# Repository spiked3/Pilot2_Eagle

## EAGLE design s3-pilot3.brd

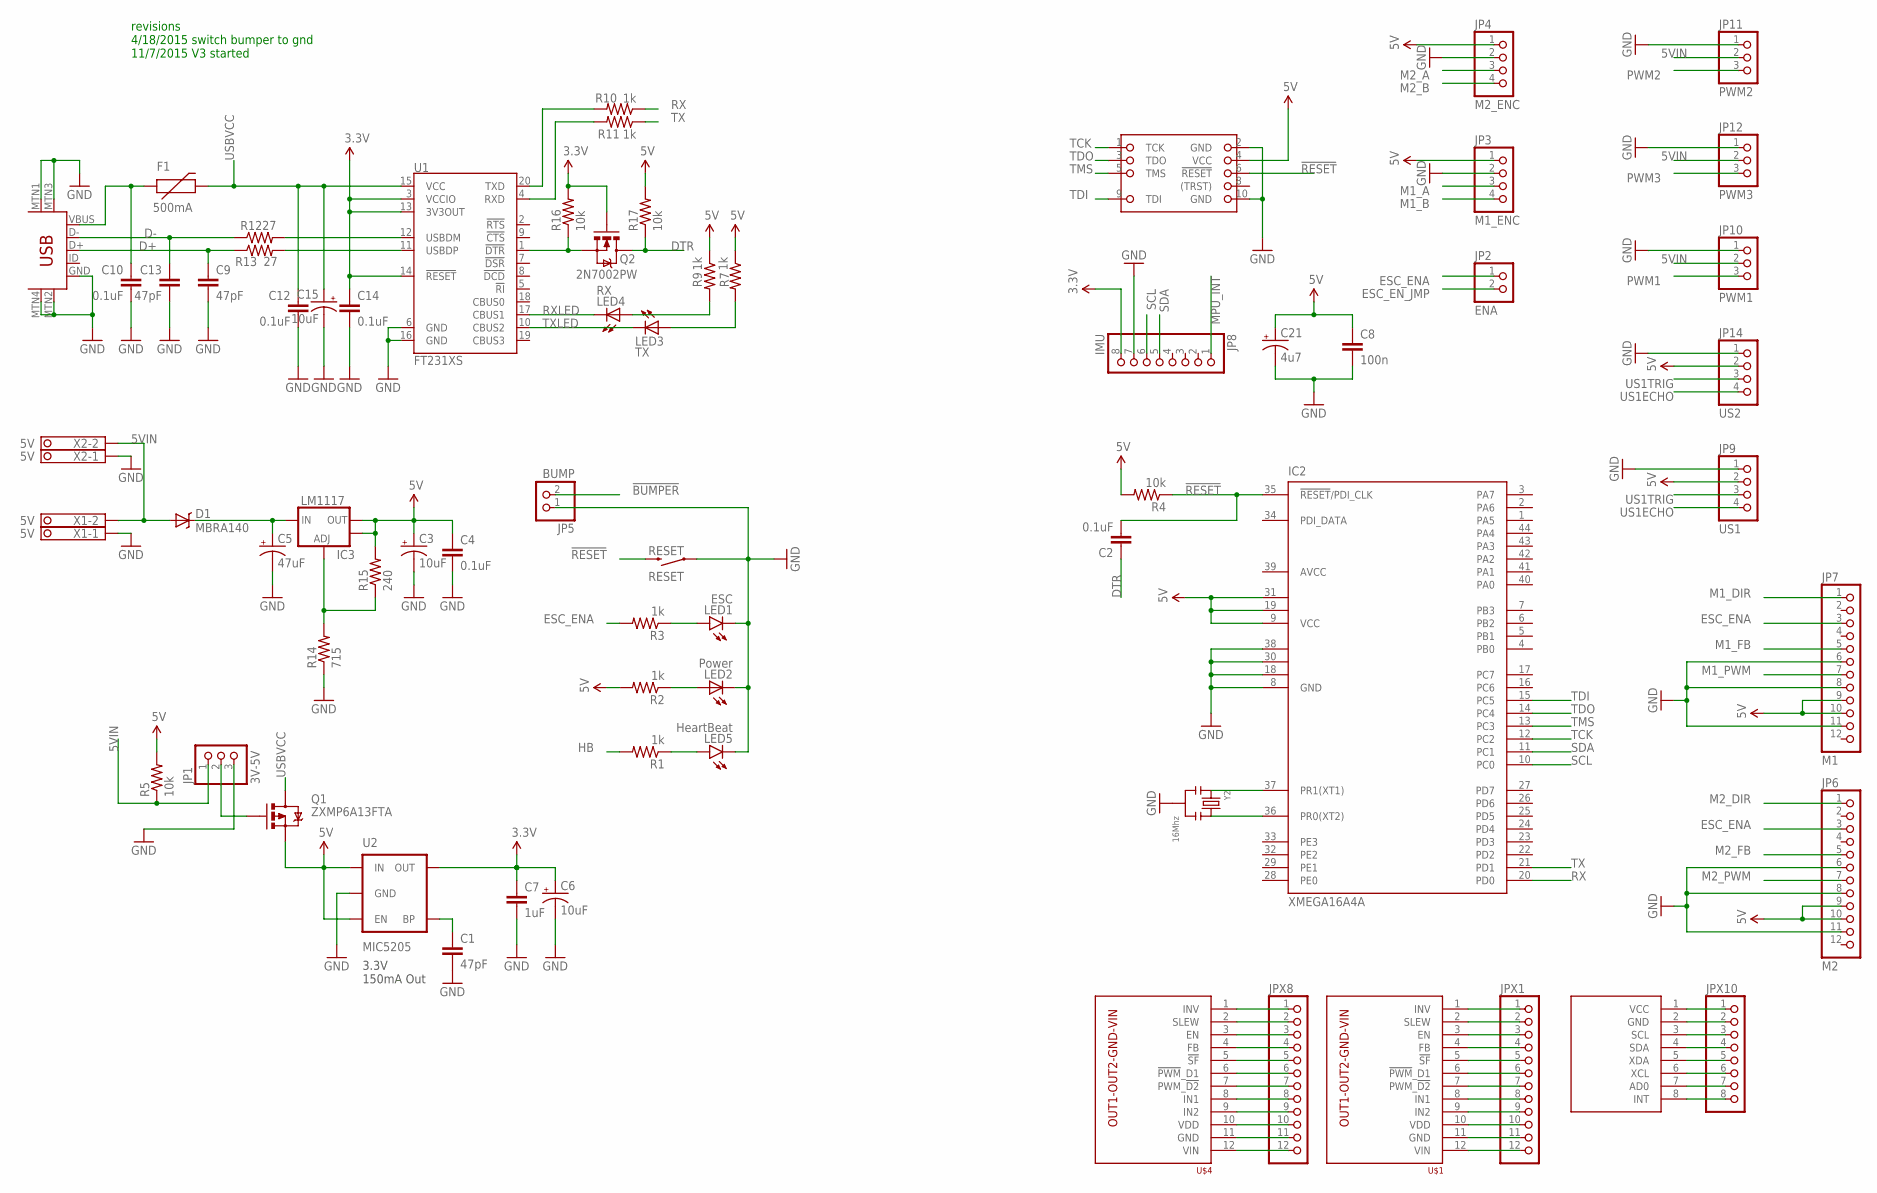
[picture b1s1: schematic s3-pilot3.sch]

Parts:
C1, C9, C13: 47pF; 0603-CAP
C2: 0.1uF; 0805
C3, C6, C15: 10uF; EIA3216
C4, C10, C12, C14: 0.1uF; 0603-CAP
C5: 47uF; PANASONIC_D
C7: 1uF; 0603-CAP
C8: 100n; 0603-CAP
C21: 4u7; EIA3216
D1: MBRA140; SMA-DIODE
F1: 500mA; PTC-1206
IC2: XMEGA16A4A; TQFP44
IC3: LM1117; SOT223
JP1: 3V-5V; 1X03
JP2: ENA; 1X02
JP3: M1_ENC; 1X04/90
JP4: M2_ENC; 1X04/90
JP5: BUMP; 1X02/90
JP6: M2; 1X12
JP7: M1; 1X12
JP8: IMU; 1X08
JP9: US1; 1X04/90
JP10: PWM1; 1X03/90
JP11: PWM2; 1X03/90
JP12: PWM3; 1X03/90
JP14: US2; 1X04/90
JPX1, JPX8: PINHD-1X12; 1X12
JPX10: PINHD-1X8; 1X08
LED1: ESC; LED-1206
LED2: Power; LED-1206
LED3: TX; LED-1206
LED4: RX; LED-1206
LED5: HeartBeat; LED-1206
MPU6050: MPU-6050-BO
Q1: ZXMP6A13FTA; SOT23-3
Q2: 2N7002PW; SOT323
R1, R2, R3, R7, R9, R10, R11: 1k; 0603-RES
R4, R5, R16, R17: 10k; 0603-RES
R12, R13: 27; 0603-RES
R14: 715; 0603-RES
R15: 240; 0603-RES
RESET: RESET; TACTILE_SWITCH_TALL
U1: FT231XS; SSOP20_L
U2: MIC5205; SOT23-5
U$1, U$4: M2; MC33926-SINGLE-BO
U$2: JTAG; 2X5/05
U$13: USB-MINIB-5PIN; USB-MINIB
X1, X2: 5V; 1751248
Y2: 16Mhz; SMD-KYOCERA-PBRV-H

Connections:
3.3V: C6.A (+), C7.1, C14.1, JP8.8, Q2.1 (G), R16.2, U1.3 (VCCIO), U1.13 (3V3OUT), U1.14 (!RESET), U2.5 (OUT)
5V: C3.A (+), C4.1, C8.1, C21.A (+), IC2.9 (VCC), IC2.19 (VCC1), IC2.31 (VCC2), IC3.2 (OUT), IC3.4 (OUT), JP3.1, JP4.1, JP6.9, JP6.10, JP7.9, JP7.10, JP9.2, JP14.2, Q1.2 (S), R2.2, R4.2, R5.2, R7.1, R9.1, R15.2, R17.2, U2.1 (IN), U2.3 (EN), U$2.4 (VCC)
5VIN: D1.A, JP1.1, JP10.2, JP11.2, JP12.2, R5.1, X1.2, X2.2
!BUMPER: JP5.2
!RESET: C2.2, IC2.35 (!RESET!/PDI_CLK), R4.1, RESET.B2 (2), U$2.6 (!RESET)
AVCC: IC2.39 (AVCC)
D+: C9.1, R13.1, U$13.D+
D-: C13.1, R12.1, U$13.D-
DTR: C2.1, Q2.3 (D), R17.1
ESC_ENA: JP2.1, JP6.3, JP7.3, R3.2
ESC_EN_JMP: JP2.2
GND: C1.2, C3.C (-), C4.2, C5.-, C6.C (-), C7.2, C8.2, C9.2, C10.2, C12.2, C13.2, C14.2, C15.C (-), C21.C (-), IC2.8 (GND), IC2.18 (GND1), IC2.30 (GND2), IC2.38 (GND3), JP1.3, JP3.2, JP4.2, JP5.1, JP6.6, JP6.8, JP6.11, JP7.6, JP7.8, JP7.11, JP8.7, JP9.1, JP10.1, JP11.1, JP12.1, JP14.1, LED1.C, LED2.C, LED5.C, R14.1, RESET.A2 (1), U1.6 (GND), U1.16 (GND), U2.2 (GND), U$2.2 (GND), U$2.10 (GND), U$13.GND, U$13.MTN1 (MTN2), U$13.MTN2 (MTN3), U$13.MTN3 (MTN1), U$13.MTN4, X1.1, X2.1, Y2.2
HB: R1.2
M1_A: JP3.3
M1_B: JP3.4
M1_DIR: JP7.1
M1_FB: JP7.5
M1_PWM: JP7.7
M2_A: JP4.3
M2_B: JP4.4
M2_DIR: JP6.1
M2_FB: JP6.5
M2_PWM: JP6.7
MPU_INT: JP8.1
unnamed: JPX8.1, U$4.1 (INV)
unnamed: LED2.A, R2.1
unnamed: JPX8.2, U$4.2 (SLEW)
unnamed: JPX8.3, U$4.3 (EN)
unnamed: R12.2, U1.12 (USBDM)
unnamed: R13.2, U1.11 (USBDP)
unnamed: LED3.A, R7.2
unnamed: LED4.A, R9.2
unnamed: C1.1, U2.4 (BP)
unnamed: Q2.2 (S), R16.1, U1.1 (!DTR)
unnamed: JPX10.1, MPU6050.1 (VCC)
unnamed: JPX10.2, MPU6050.2 (GND)
unnamed: IC3.1 (ADJ), R14.2, R15.1
unnamed: JPX10.3, MPU6050.3 (SCL)
unnamed: JPX10.4, MPU6050.4 (SDA)
unnamed: JPX1.1, U$1.1 (INV)
unnamed: JPX10.5, MPU6050.5 (XDA)
unnamed: JPX10.6, MPU6050.6 (XCL)
unnamed: LED5.A, R1.1
unnamed: JPX10.7, MPU6050.7 (AD0)
unnamed: LED1.A, R3.1
unnamed: JP1.2, Q1.1 (G)
unnamed: JPX1.2, U$1.2 (SLEW)
unnamed: JPX10.8, MPU6050.8 (INT)
unnamed: JPX8.4, U$4.4 (FB)
unnamed: JPX8.5, U$4.5 (!SF)
unnamed: JPX8.6, U$4.6 (!PWM!_D1)
unnamed: JPX8.7, U$4.7 (PWM_!D2)
unnamed: JPX8.8, U$4.8 (IN1)
unnamed: JPX8.9, U$4.9 (IN2)
unnamed: JPX8.10, U$4.10 (VDD)
unnamed: JPX8.11, U$4.11 (GND)
unnamed: JPX8.12, U$4.12 (VIN)
unnamed: IC2.36 (PR0(XT2)), Y2.3
unnamed: JPX1.3, U$1.3 (EN)
unnamed: JPX1.4, U$1.4 (FB)
unnamed: JPX1.5, U$1.5 (!SF)
unnamed: IC2.37 (PR1(XT1)), Y2.1
unnamed: JPX1.6, U$1.6 (!PWM!_D1)
unnamed: JPX1.7, U$1.7 (PWM_!D2)
unnamed: JPX1.8, U$1.8 (IN1)
unnamed: JPX1.9, U$1.9 (IN2)
unnamed: JPX1.10, U$1.10 (VDD)
unnamed: JPX1.11, U$1.11 (GND)
unnamed: JPX1.12, U$1.12 (VIN)
PISUPPLY: C5.+, D1.C, IC3.3 (IN)
PWM1: JP10.3
PWM2: JP11.3
PWM3: JP12.3
RX: IC2.20 (PD0), R10.1
RXD: R11.2, U1.4 (RXD)
RXLED: LED4.C, U1.17 (CBUS1)
SCL: IC2.10 (PC0), JP8.6
SDA: IC2.11 (PC1), JP8.5
TCK: IC2.12 (PC2), U$2.1 (TCK)
TDI: IC2.15 (PC5), U$2.9 (TDI)
TDO: IC2.14 (PC4), U$2.3 (TDO)
TMS: IC2.13 (PC3), U$2.5 (TMS)
TX: IC2.21 (PD1), R11.1
TXD: R10.2, U1.20 (TXD)
TXLED: LED3.C, U1.10 (CBUS2)
US1ECHO: JP9.4, JP14.4
US1TRIG: JP9.3, JP14.3
USBVCC: C12.1, C15.A (+), F1.2, Q1.3 (D), U1.15 (VCC)
VUSB: C10.1, F1.1, U$13.VBUS

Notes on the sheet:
revisions 4/18/2015 switch bumper to gnd 11/7/2015 V3 started
3.3V 150mA Out

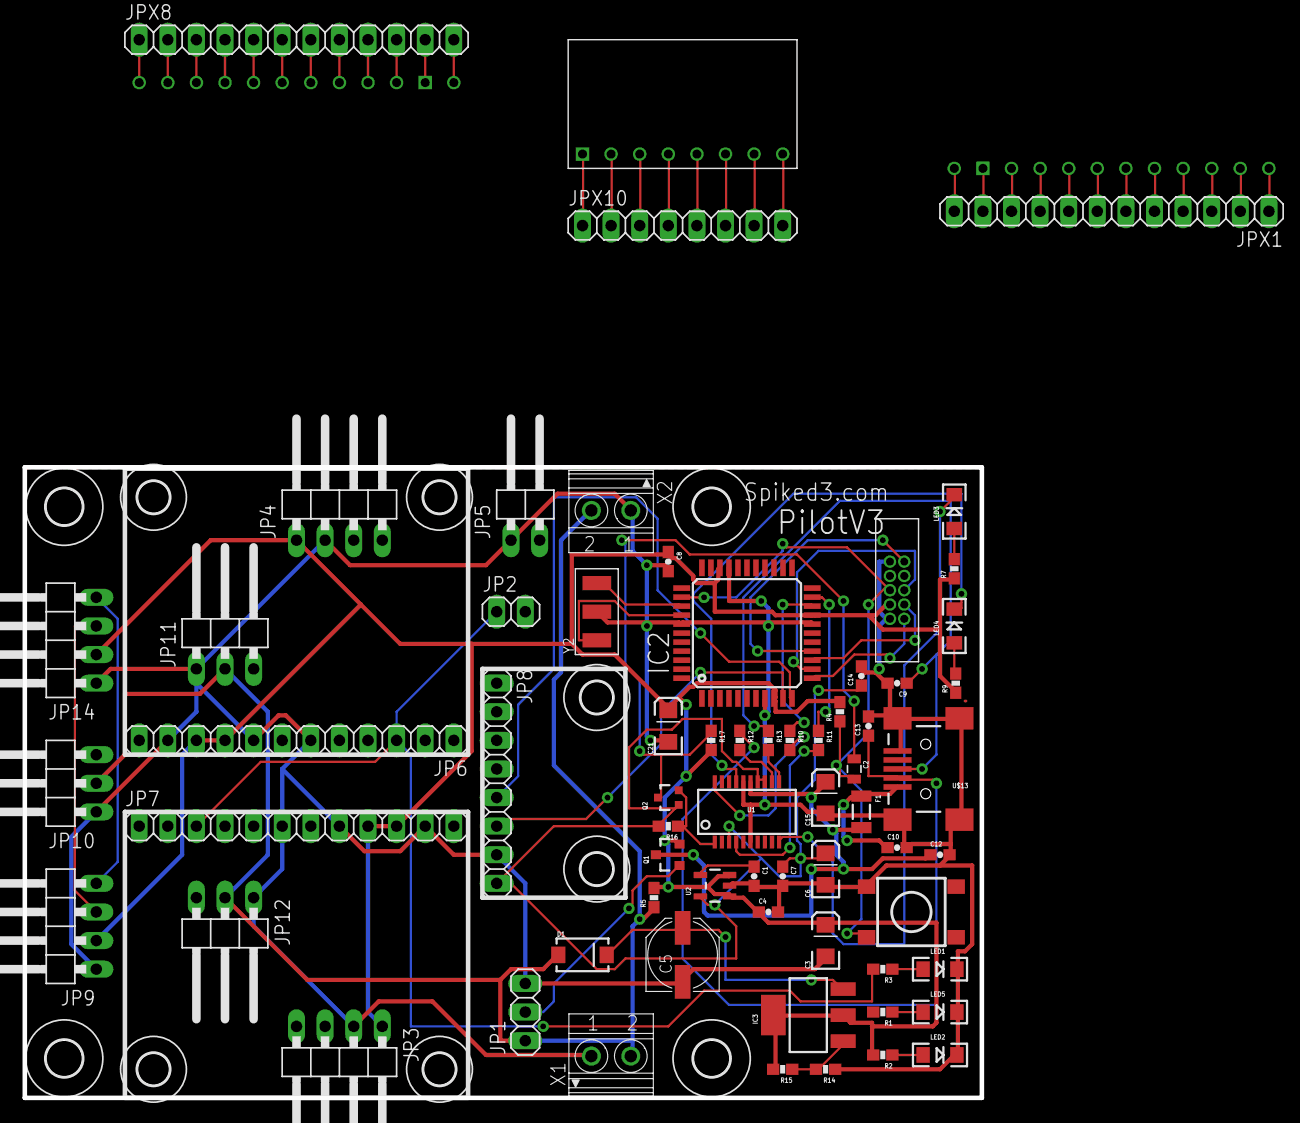
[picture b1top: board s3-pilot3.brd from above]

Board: 2 copper layers, 85.0 x 56.0 mm, 78 parts (0 on the bottom side), 71 nets.

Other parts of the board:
E$1, E$4, E$12, E$15, E$16, E$17: 2,8
E$2, E$3, E$5, E$6: 3,2

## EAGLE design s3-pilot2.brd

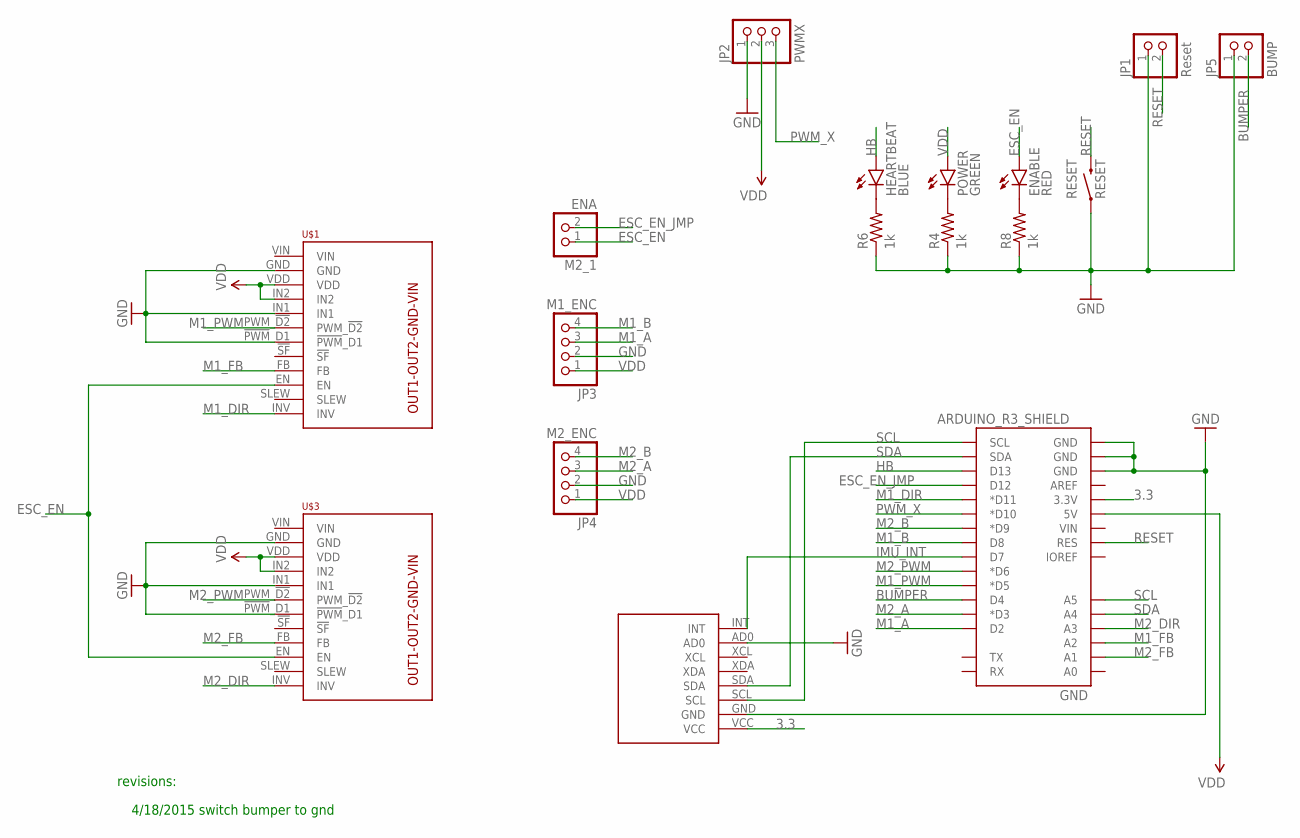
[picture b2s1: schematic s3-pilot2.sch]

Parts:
ENABLE: RED; LED-1206
GND: ARDUINO_R3_SHIELD; UNO_R3_SHIELD
HEARTBEAT: BLUE; LED-1206
JP1: Reset; 1X02
JP2: PWMX; 1X03/90
JP3: M1_ENC; 1X04/90
JP4: M2_ENC; 1X04/90
JP5: BUMP; 1X02/90
M2_1: ENA; 1X02
MPU6050: MPU-6050-BO
POWER: GREEN; LED-1206
R4, R6, R8: 1k; 1206
RESET: RESET; TACTILE_SWITCH_TALL
U$1: M1; MC33926-SINGLE-BO
U$3: M2; MC33926-SINGLE-BO

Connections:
3.3: GND.3.3V, MPU6050.VCC
BUMPER: GND.D4, JP5.2
ESC_EN: ENABLE.A, M2_1.1, U$1.EN, U$3.EN
ESC_EN_JMP: GND.D12, M2_1.2
GND: GND.GND@0 (GND), GND.GND@1 (GND), GND.GND@2 (GND), JP1.1, JP2.1, JP3.2, JP4.2, JP5.1, MPU6050.AD0, MPU6050.GND, R4.1, R6.1, R8.1, RESET.A2 (1), U$1.!PWM!_D1, U$1.GND, U$1.IN1, U$3.!PWM!_D1, U$3.GND, U$3.IN1
HB: GND.D13, HEARTBEAT.A
IMU_INT: GND.D7, MPU6050.INT
M1_A: GND.D2, JP3.3
M1_B: GND.D8, JP3.4
M1_DIR: GND.D11 (*D11), U$1.INV
M1_FB: GND.A2, U$1.FB
M1_PWM: GND.D5 (*D5), U$1.PWM_!D2
M2_A: GND.D3 (*D3), JP4.3
M2_B: GND.D9 (*D9), JP4.4
M2_DIR: GND.A3, U$3.INV
M2_FB: GND.A1, U$3.FB
M2_PWM: GND.D6 (*D6), U$3.PWM_!D2
unnamed: POWER.C, R4.2
unnamed: ENABLE.C, R8.2
unnamed: HEARTBEAT.C, R6.2
PWM_X: GND.D10 (*D10), JP2.3
RESET: GND.RES, JP1.2, RESET.B2 (2)
SCL: GND.A5, GND.SCL, MPU6050.SCL
SDA: GND.A4, GND.SDA, MPU6050.SDA
VDD: GND.5V, JP2.2, JP3.1, JP4.1, POWER.A, U$1.IN2, U$1.VDD, U$3.IN2, U$3.VDD

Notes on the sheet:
revisions:
4/18/2015 switch bumper to gnd

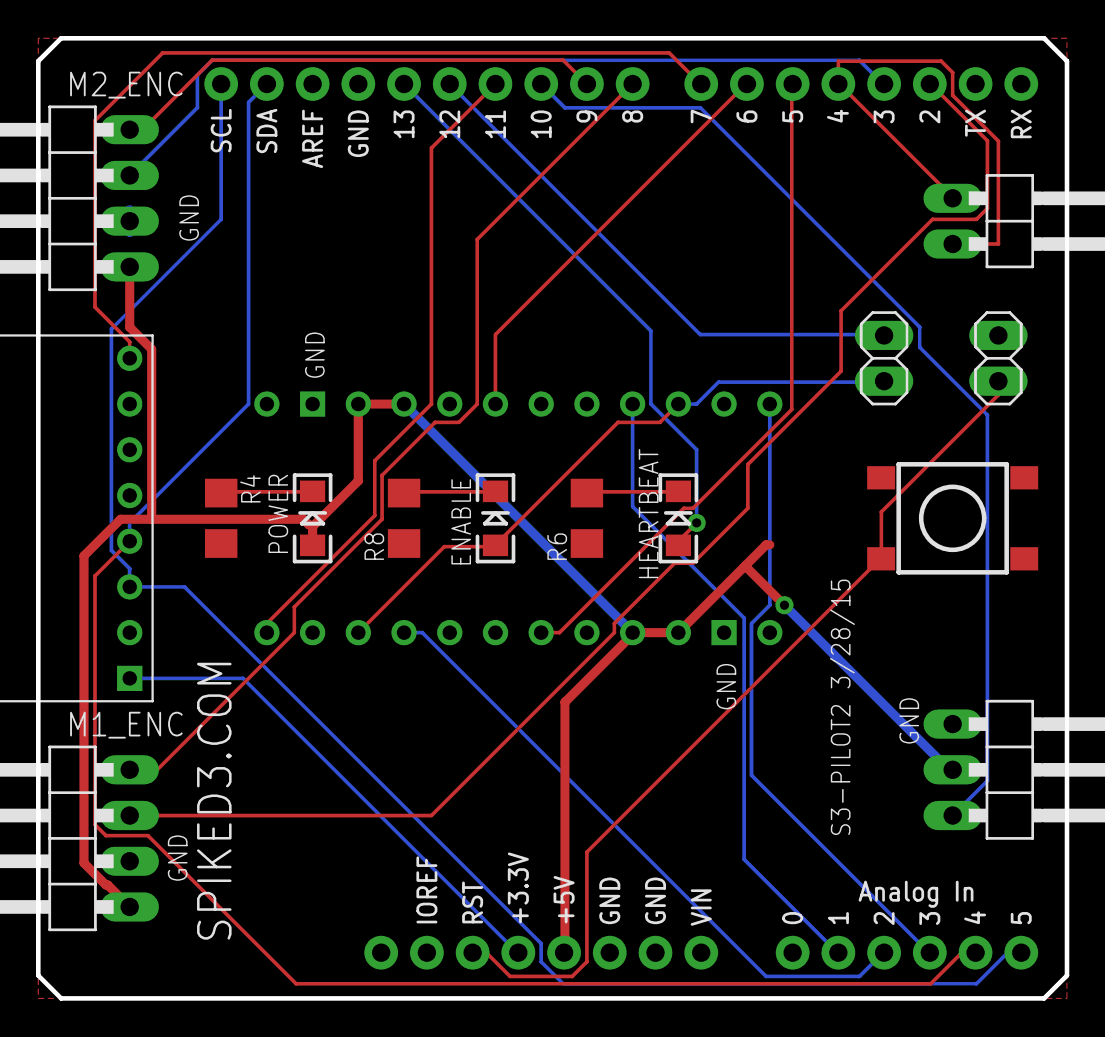
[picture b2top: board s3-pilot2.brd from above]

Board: 2 copper layers, 57.1 x 53.3 mm, 17 parts (0 on the bottom side), 25 nets.

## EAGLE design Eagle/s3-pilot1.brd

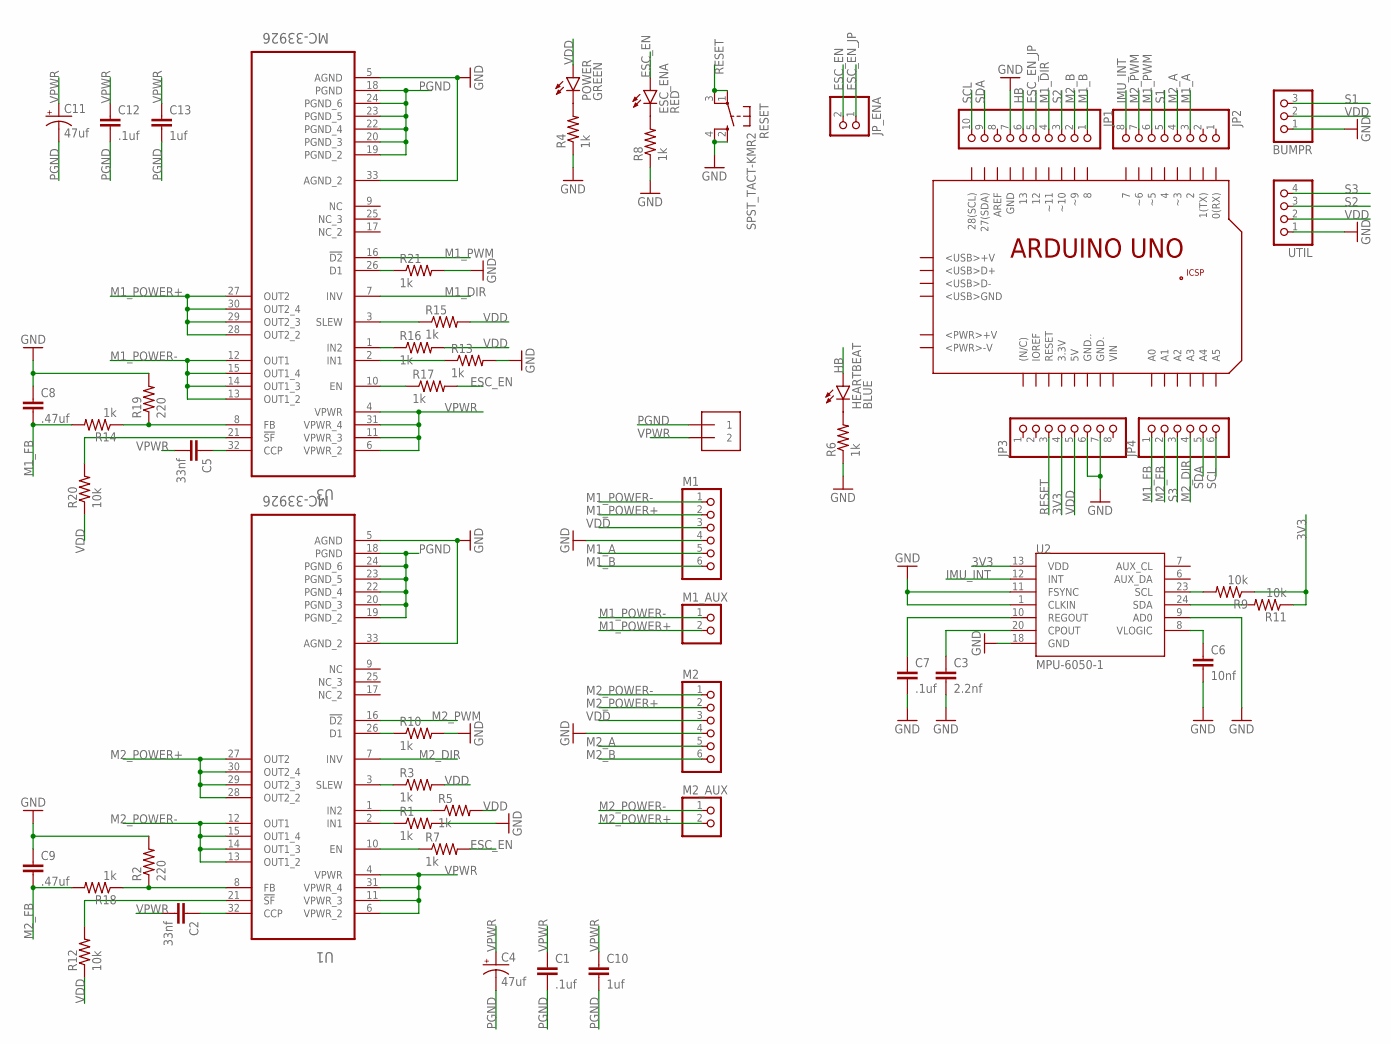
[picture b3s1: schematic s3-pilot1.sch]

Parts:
BUMPR: PINHD-1X3/90; 1X03/90
C1, C7, C12: .1uf; 0805
C2, C5: 33nf; 0805
C3: 2.2nf; 0805
C4, C11: 47uf; PANASONIC_D
C6: 10nf; 0805
C8, C9: .47uf; 0805
C10, C13: 1uf; 0805
ESC_ENA: RED; LED-0603
HEARTBEAT: BLUE; LED-0603
JP1: PINHD-1X10; 1X10
JP2, JP3: PINHD-1X8; 1X08
JP4: PINHD-1X6; 1X06
JP_ENA: PINHD-1X2; 1X02
M1, M2: PINHD-1X6/90; 1X06/90
M1_AUX, M2_AUX: PINHD-1X2/90; 1X02/90
MOTOR_POWER_IN: 1X2-3.5MM
POWER: GREEN; LED-0603
R1, R3, R4, R5, R6, R7, R8, R10, R13, R14, R15, R16, R17, R18, R21: 1k; 0805
R2, R19: 220; 0805
R9, R11, R12, R20: 10k; 0805
RESET: SPST_TACT-KMR2; KMR2
U1, U3: MC-33926; QFN80P800X800X220-33N
U2: MPU-6050-1; QFN-24-4MM2
UTIL: PINHD-1X4/90; 1X04/90

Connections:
3V3: JP3.4, R9.1, R11.1, U2.13 (VDD)
AGND: U1.5 (AGND), U1.33 (AGND_2)
ESC_EN: ESC_ENA.A, JP_ENA.2, R7.2, R17.2
ESC_EN_JP: JP1.5, JP_ENA.1
GND: BUMPR.1, C3.2, C6.2, C7.2, C8.1, C9.1, JP1.7, JP3.6, JP3.7, M1.4, M2.4, R1.2, R2.2, R4.1, R6.1, R8.1, R10.2, R13.2, R19.2, R21.2, RESET.2 (S), RESET.4 (S1), U2.1 (CLKIN), U2.9 (AD0), U2.11 (FSYNC), U2.18 (GND), U3.5 (AGND), U3.33 (AGND_2), UTIL.1
HB: HEARTBEAT.A, JP1.6
IMU_INT: JP2.8, U2.12 (INT)
M1_A: JP2.3, M1.5
M1_B: JP1.1, M1.6
M1_DIR: JP1.4, U3.7 (INV)
M1_FB: C8.2, JP4.1, R14.2
M1_POWER+: M1.2, M1_AUX.2, U3.27 (OUT2), U3.28 (OUT2_2), U3.29 (OUT2_3), U3.30 (OUT2_4)
M1_POWER-: M1.1, M1_AUX.1, U3.12 (OUT1), U3.13 (OUT1_2), U3.14 (OUT1_3), U3.15 (OUT1_4)
M1_PWM: JP2.6, U3.16 (!D2)
M2_A: JP2.4, M2.5
M2_B: JP1.2, M2.6
M2_DIR: JP4.4, U1.7 (INV)
M2_FB: C9.2, JP4.2, R18.2
M2_POWER+: M2.2, M2_AUX.2, U1.27 (OUT2), U1.28 (OUT2_2), U1.29 (OUT2_3), U1.30 (OUT2_4)
M2_POWER-: M2.1, M2_AUX.1, U1.12 (OUT1), U1.13 (OUT1_2), U1.14 (OUT1_3), U1.15 (OUT1_4)
M2_PWM: JP2.7, U1.16 (!D2)
unnamed: R17.1, U3.10 (EN)
unnamed: R10.1, U1.26 (D1)
unnamed: R3.1, U1.3 (SLEW)
unnamed: R15.1, U3.3 (SLEW)
unnamed: C5.1, U3.32 (CCP)
unnamed: C2.1, U1.32 (CCP)
unnamed: R7.1, U1.10 (EN)
unnamed: R5.1, U1.1 (IN2)
unnamed: R1.1, U1.2 (IN1)
unnamed: R16.1, U3.1 (IN2)
unnamed: R21.1, U3.26 (D1)
unnamed: R13.1, U3.2 (IN1)
unnamed: R12.2, U1.21 (!SF)
unnamed: R20.2, U3.21 (!SF)
unnamed: C3.1, U2.20 (CPOUT)
unnamed: C7.1, U2.10 (REGOUT)
unnamed: C6.1, U2.8 (VLOGIC)
unnamed: R2.1, R18.1, U1.8 (FB)
unnamed: POWER.C, R4.2
unnamed: R14.1, R19.1, U3.8 (FB)
unnamed: ESC_ENA.C, R8.2
unnamed: HEARTBEAT.C, R6.2
PGND: C1.2, C4.-, C10.2, C11.-, C12.2, C13.2, MOTOR_POWER_IN.1, U1.18 (PGND), U1.19 (PGND_2), U1.20 (PGND_3), U1.22 (PGND_4), U1.23 (PGND_5), U1.24 (PGND_6), U3.18 (PGND), U3.19 (PGND_2), U3.20 (PGND_3), U3.22 (PGND_4), U3.23 (PGND_5), U3.24 (PGND_6)
RESET: JP3.3, RESET.1, RESET.3 (P1)
S1: BUMPR.3, JP2.5
S2: JP1.3, UTIL.3
S3: JP4.3, UTIL.4
SCL: JP1.10, JP4.6, R9.2, U2.23 (SCL)
SDA: JP1.9, JP4.5, R11.2, U2.24 (SDA)
VDD: BUMPR.2, JP3.5, M1.3, M2.3, POWER.A, R3.2, R5.2, R12.1, R15.2, R16.2, R20.1, UTIL.2
VPWR: C1.1, C2.2, C4.+, C5.2, C10.1, C11.+, C12.1, C13.1, MOTOR_POWER_IN.2, U1.4 (VPWR), U1.6 (VPWR_2), U1.11 (VPWR_3), U1.31 (VPWR_4), U3.4 (VPWR), U3.6 (VPWR_2), U3.11 (VPWR_3), U3.31 (VPWR_4)

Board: 2 copper layers, 53 parts (0 on the bottom side), 52 nets, no tracks yet.

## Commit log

2015-03-29 initial
2015-03-30 OSPARK order 3/29/15
2015-03-30 file sent to ITEAD
2015-04-17 cleanup
2015-04-19 update bumper switch
2015-11-23 started new version.
2015-12-05 final mounting hole position on bd.
2015-12-22 removed full 644 spec (large)

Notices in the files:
parts and their libraries:
SparkFun-Capacitors: Licensing: Creative Commons ShareAlike 4.0 International - https://creativecommons.org/licenses/by-sa/4.0
SparkFun-Capacitors: Licensing: CC v3.0 Share-Alike You are welcome to use this library for commercial purposes.
